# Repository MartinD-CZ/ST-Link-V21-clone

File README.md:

# ST-Link V2.1 USB dongle
This is an ST-Link V2.1 in the form of an USB dongle, similar to those available from any Chinese store. However, the IDC connector has different pinout, with the following pins available:
- +5 V and +3.3 V, each up to 500 mA
- TPWR for measuring target voltage or future optoisolators
- GND
- SSWCLK, SWDIO, NRST for programming/debugging
- SWO for SW Trace functionality
- RX/TX for VCP (Virtual Com Port)

[**MORE INFO**](http://embedblog.eu/?p=780)

### Update 05/21
I've made another version, this time with an SMD crystal and a microUSB connector - it's marked as rev10D.

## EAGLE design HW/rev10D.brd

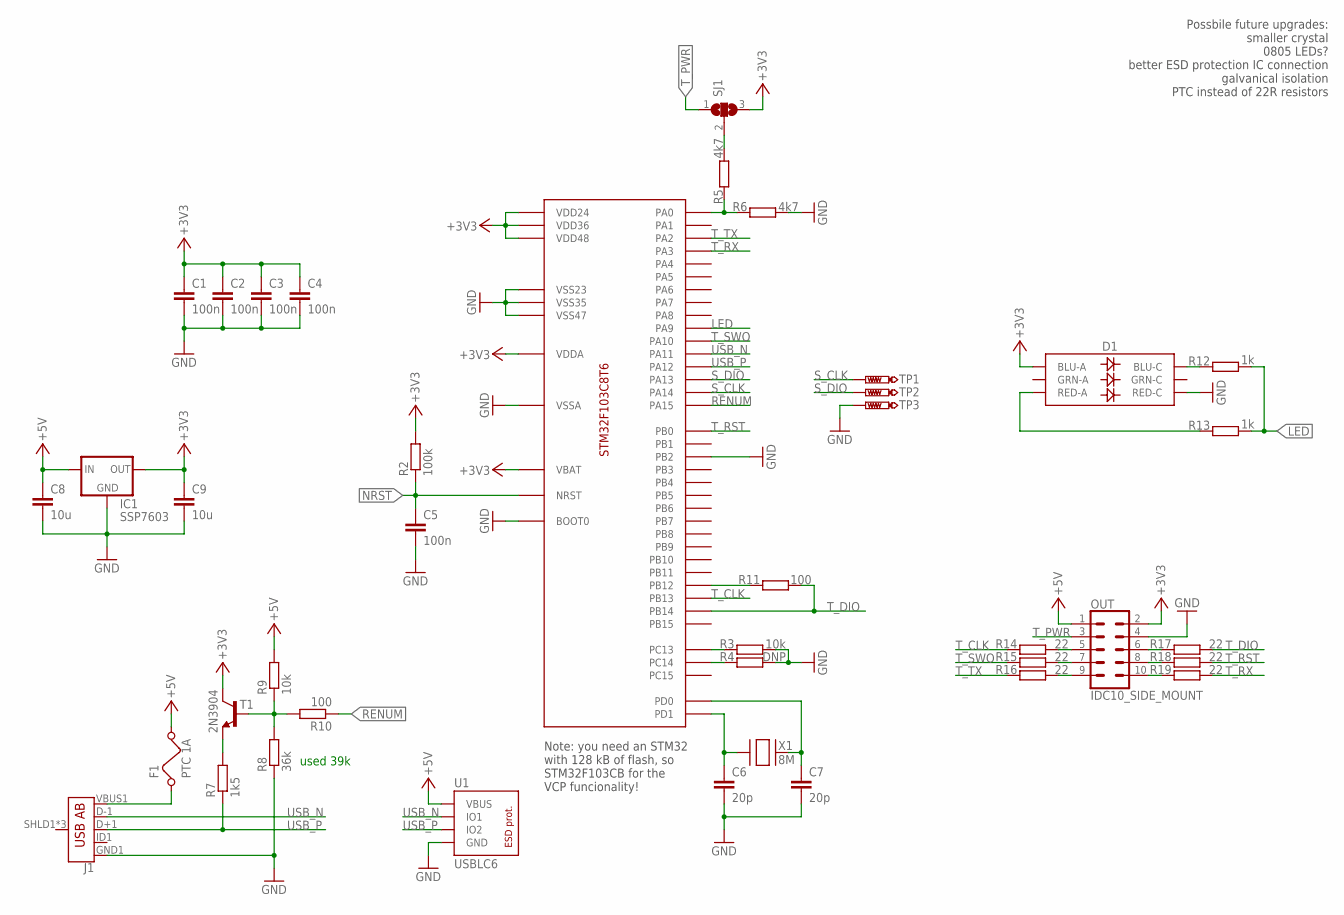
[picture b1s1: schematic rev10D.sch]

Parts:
C1, C2, C3, C4, C5: 100n; C0603
C6, C7: 20p; C0805
C8, C9: 10u; C0805
D1: LED-RGBNO_IC; LED-TRICOLOR-5050
F1: PTC 1A; 0805
IC1: SSP7603; SOT23
IC2: STM32F103C8T6; TQFP-48
J1: USB_AB_SMT; USB-AB-MICRO-SMD
OUT: IDC10_SIDE_MOUNT; IDC10_SIDEWAYS
R2: 100k; R0805
R3, R9: 10k; R0805
R4: DNP; R0805
R5, R6: 4k7; R0805
R7: 1k5; R0805
R8: 36k; R0805
R10, R11: 100; R0805
R12, R13: 1k; R0805
R14, R15, R16, R17, R18, R19: 22; R0805
SJ1: SJ2W; SJ_2
T1: 2N3904; SOT23-BEC
TP1, TP2, TP3: PTR1B1,27; B1,27
U1: USBLC6; SOT23-6
X1: 8M; NX5032

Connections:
+3V3: C1.1, C2.1, C3.1, C4.1, C9.1, D1.3 (BLU-A), IC1.2 (OUT), IC2.1 (VBAT), IC2.9 (VDDA), IC2.24 (VDD24), IC2.36 (VDD36), IC2.48 (VDD48), OUT.2, R2.2, SJ1.3, T1.C
+5V: C8.1, F1.2, IC1.3 (IN), OUT.1, R9.2, U1.5 (VBUS)
GND: C1.2, C2.2, C3.2, C4.2, C5.2, C6.2, C7.2, C8.2, C9.2, D1.5 (RED-C), IC1.1 (GND), IC2.8 (VSSA), IC2.20 (PB2), IC2.23 (VSS23), IC2.35 (VSS35), IC2.44 (BOOT0), IC2.47 (VSS47), J1.GND1 (GND), OUT.4, R3.1, R4.1, R6.1, R8.1, TP3.TP, U1.2 (GND)
LED: IC2.30 (PA9), R12.1, R13.1
unnamed: IC2.3 (PC14), R4.2
unnamed: IC2.25 (PB12), R11.2
unnamed: IC2.2 (PC13), R3.2
unnamed: C6.1, IC2.6 (PD1), X1.P$1
unnamed: C7.1, IC2.5 (PD0), X1.P$2
unnamed: R7.2, T1.E
unnamed: IC2.10 (PA0), R5.2, R6.2
unnamed: F1.1, J1.VBUS1 (VBUS)
unnamed: R8.2, R9.1, R10.2, T1.B
unnamed: D1.2 (RED-A), R13.2
unnamed: D1.4 (BLU-C), R12.2
unnamed: R5.1, SJ1.2
unnamed: OUT.5, R14.1
unnamed: OUT.7, R15.1
unnamed: OUT.9, R16.1
unnamed: OUT.6, R17.2
unnamed: OUT.8, R18.2
unnamed: OUT.10, R19.2
NRST: C5.1, IC2.7 (NRST), R2.1
RENUM: IC2.38 (PA15), R10.1
S_CLK: IC2.37 (PA14), TP1.TP
S_DIO: IC2.34 (PA13), TP2.TP
T_CLK: IC2.26 (PB13), R14.2
T_DIO: IC2.27 (PB14), R11.1, R17.1
T_PWR: OUT.3, SJ1.1
T_RST: IC2.18 (PB0), R18.1
T_RX: IC2.13 (PA3), R19.1
T_SWO: IC2.31 (PA10), R15.2
T_TX: IC2.12 (PA2), R16.2
USB_N: IC2.32 (PA11), J1.D-1 (D-), U1.1 (IO1), U1.6 (IO1)
USB_P: IC2.33 (PA12), J1.D+1 (D+), R7.1, U1.3 (IO2), U1.4 (IO2)

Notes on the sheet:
Possbile future upgrades: smaller crystal 0805 LEDs? better ESD protection IC connection galvanical isolation PTC instead of 22R resistors
Note: you need an STM32 with 128 kB of flash, so STM32F103CB for the VCP funcionality!
used 39k

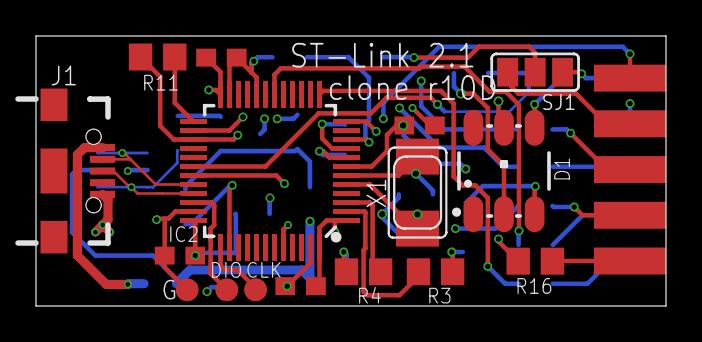
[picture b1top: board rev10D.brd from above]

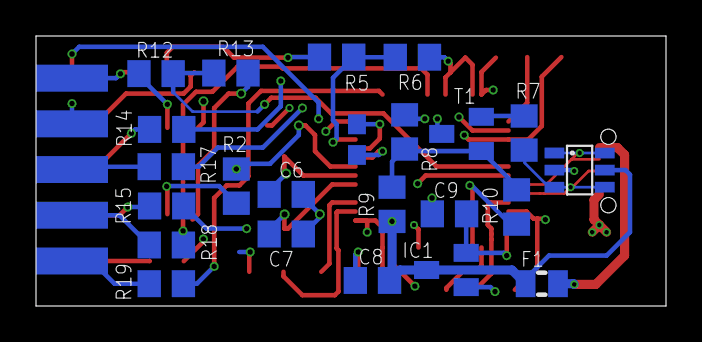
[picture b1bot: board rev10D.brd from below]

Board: 4 copper layers, 35.0 x 15.0 mm, 40 parts (23 on the bottom side), 35 nets.

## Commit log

2021-03-03 initial
2021-05-22 added rev10D
    A new version, with an SMD crystal, micro USB and some minor tweaks

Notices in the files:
parts and their libraries:
SparkFun-LED: Licensing: Creative Commons ShareAlike 4.0 International - https://creativecommons.org/licenses/by-sa/4.0
m-pad-2.1: License : GNU General Public License version 2 (see bottom)
